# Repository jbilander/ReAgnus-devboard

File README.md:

# ReAgnus-devboard
A development board for ReAgnus<br />

Compatible with the [PLCC-84-plug](https://github.com/jbilander/PLCC-84-plug)

With this board you can signal tap a real Agnus chip by having a real Agnus IC in one socket and ReAgnus in the other.

***

REV 1C

<br />

<br />

<br />

<br />

***

[![CC BY-SA 4.0][cc-by-sa-shield]][cc-by-sa]

This work is licensed under a
[Creative Commons Attribution-ShareAlike 4.0 International License][cc-by-sa].

[![CC BY-SA 4.0][cc-by-sa-image]][cc-by-sa]

[cc-by-sa]: http://creativecommons.org/licenses/by-sa/4.0/
[cc-by-sa-image]: https://licensebuttons.net/l/by-sa/4.0/88x31.png
[cc-by-sa-shield]: https://img.shields.io/badge/License-CC%20BY--SA%204.0-lightgrey.svg

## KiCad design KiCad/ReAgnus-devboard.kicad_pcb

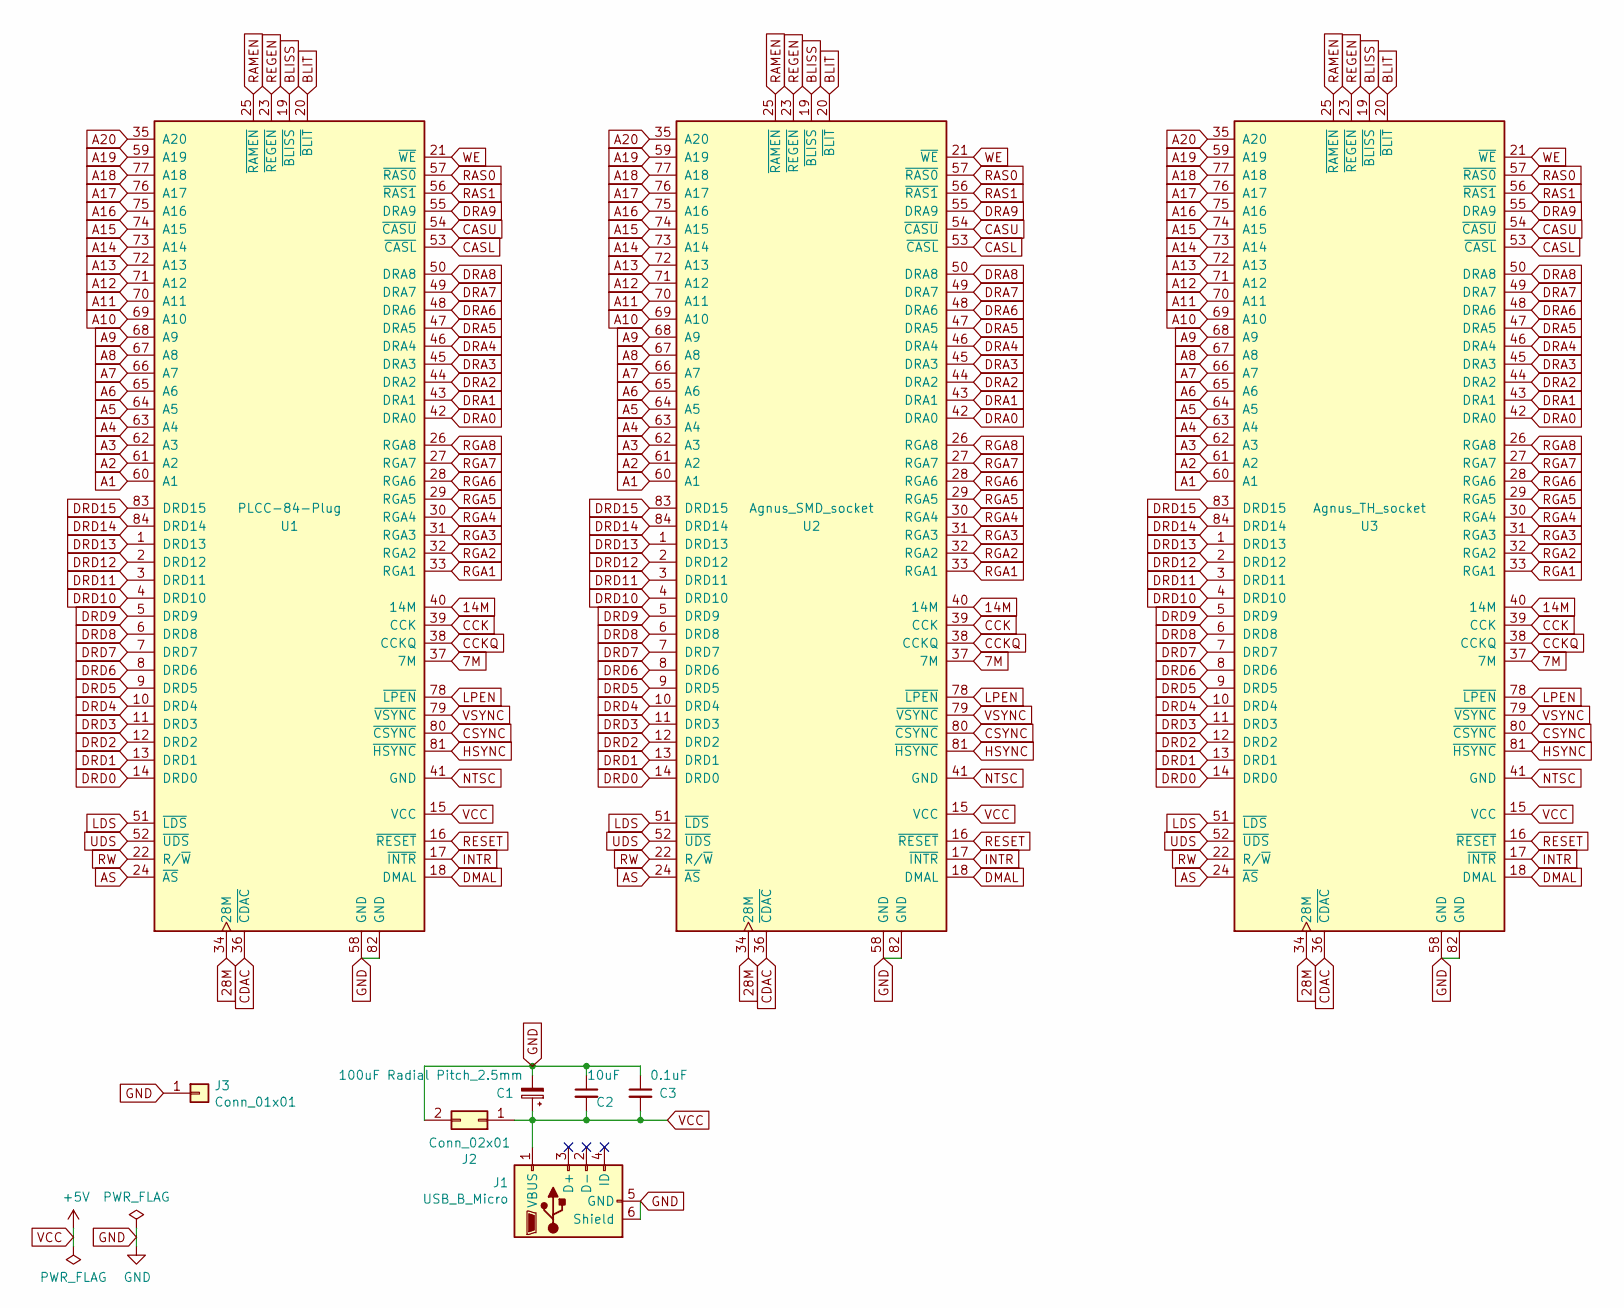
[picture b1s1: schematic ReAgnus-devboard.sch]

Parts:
C1: 100uF Radial Pitch_2.5mm; CP_Radial_D5.0mm_P2.50mm
C2: 10uF; C_1206_3216Metric_Pad1.33x1.80mm_HandSolder
C3: 0.1uF; C_0805_2012Metric_Pad1.18x1.45mm_HandSolder
J1: USB_B_Micro; USB_Micro-B_Unknown_5s_SMT
J2: Conn_02x01; PinHeader_2x01_P2.54mm_Vertical
J3: Conn_01x01; MountingHole_3.2mm_M3_Pad_Via
U1: PLCC-84-Plug; PLCC-84_Plug_P1.27mm_mirrored
U2: Agnus_SMD_socket; PLCC-84_SMD-Socket_TH_modded
U3: Agnus_TH_socket; PLCC-84_THT-Socket

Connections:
7M: U1.37 (7M), U2.37 (7M), U3.37 (7M)
14M: U1.40 (14M), U2.40 (14M), U3.40 (14M)
28M: U1.34 (28M), U2.34 (28M), U3.34 (28M)
A1: U1.60 (A1), U2.60 (A1), U3.60 (A1)
A2: U1.61 (A2), U2.61 (A2), U3.61 (A2)
A3: U1.62 (A3), U2.62 (A3), U3.62 (A3)
A4: U1.63 (A4), U2.63 (A4), U3.63 (A4)
A5: U1.64 (A5), U2.64 (A5), U3.64 (A5)
A6: U1.65 (A6), U2.65 (A6), U3.65 (A6)
A7: U1.66 (A7), U2.66 (A7), U3.66 (A7)
A8: U1.67 (A8), U2.67 (A8), U3.67 (A8)
A9: U1.68 (A9), U2.68 (A9), U3.68 (A9)
A10: U1.69 (A10), U2.69 (A10), U3.69 (A10)
A11: U1.70 (A11), U2.70 (A11), U3.70 (A11)
A12: U1.71 (A12), U2.71 (A12), U3.71 (A12)
A13: U1.72 (A13), U2.72 (A13), U3.72 (A13)
A14: U1.73 (A14), U2.73 (A14), U3.73 (A14)
A15: U1.74 (A15), U2.74 (A15), U3.74 (A15)
A16: U1.75 (A16), U2.75 (A16), U3.75 (A16)
A17: U1.76 (A17), U2.76 (A17), U3.76 (A17)
A18: U1.77 (A18), U2.77 (A18), U3.77 (A18)
A19: U1.59 (A19), U2.59 (A19), U3.59 (A19)
A20: U1.35 (A20), U2.35 (A20), U3.35 (A20)
AS: U1.24 (~AS), U2.24 (~AS), U3.24 (~AS)
BLISS: U1.19 (~BLISS), U2.19 (~BLISS), U3.19 (~BLISS)
BLIT: U1.20 (~BLIT), U2.20 (~BLIT), U3.20 (~BLIT)
CASL: U1.53 (~CASL), U2.53 (~CASL), U3.53 (~CASL)
CASU: U1.54 (~CASU), U2.54 (~CASU), U3.54 (~CASU)
CCK: U1.39 (CCK), U2.39 (CCK), U3.39 (CCK)
CCKQ: U1.38 (CCKQ), U2.38 (CCKQ), U3.38 (CCKQ)
CDAC: U1.36 (~CDAC), U2.36 (~CDAC), U3.36 (~CDAC)
CSYNC: U1.80 (~CSYNC), U2.80 (~CSYNC), U3.80 (~CSYNC)
DMAL: U1.18 (DMAL), U2.18 (DMAL), U3.18 (DMAL)
DRA0: U1.42 (DRA0), U2.42 (DRA0), U3.42 (DRA0)
DRA1: U1.43 (DRA1), U2.43 (DRA1), U3.43 (DRA1)
DRA2: U1.44 (DRA2), U2.44 (DRA2), U3.44 (DRA2)
DRA3: U1.45 (DRA3), U2.45 (DRA3), U3.45 (DRA3)
DRA4: U1.46 (DRA4), U2.46 (DRA4), U3.46 (DRA4)
DRA5: U1.47 (DRA5), U2.47 (DRA5), U3.47 (DRA5)
DRA6: U1.48 (DRA6), U2.48 (DRA6), U3.48 (DRA6)
DRA7: U1.49 (DRA7), U2.49 (DRA7), U3.49 (DRA7)
DRA8: U1.50 (DRA8), U2.50 (DRA8), U3.50 (DRA8)
DRA9: U1.55 (DRA9), U2.55 (DRA9), U3.55 (DRA9)
DRD0: U1.14 (DRD0), U2.14 (DRD0), U3.14 (DRD0)
DRD1: U1.13 (DRD1), U2.13 (DRD1), U3.13 (DRD1)
DRD2: U1.12 (DRD2), U2.12 (DRD2), U3.12 (DRD2)
DRD3: U1.11 (DRD3), U2.11 (DRD3), U3.11 (DRD3)
DRD4: U1.10 (DRD4), U2.10 (DRD4), U3.10 (DRD4)
DRD5: U1.9 (DRD5), U2.9 (DRD5), U3.9 (DRD5)
DRD6: U1.8 (DRD6), U2.8 (DRD6), U3.8 (DRD6)
DRD7: U1.7 (DRD7), U2.7 (DRD7), U3.7 (DRD7)
DRD8: U1.6 (DRD8), U2.6 (DRD8), U3.6 (DRD8)
DRD9: U1.5 (DRD9), U2.5 (DRD9), U3.5 (DRD9)
DRD10: U1.4 (DRD10), U2.4 (DRD10), U3.4 (DRD10)
DRD11: U1.3 (DRD11), U2.3 (DRD11), U3.3 (DRD11)
DRD12: U1.2 (DRD12), U2.2 (DRD12), U3.2 (DRD12)
DRD13: U1.1 (DRD13), U2.1 (DRD13), U3.1 (DRD13)
DRD14: U1.84 (DRD14), U2.84 (DRD14), U3.84 (DRD14)
DRD15: U1.83 (DRD15), U2.83 (DRD15), U3.83 (DRD15)
GND: C1.2, C2.1, C3.1, J1.5 (GND), J1.6 (Shield), J2.2, J3.1, U1.58 (GND), U1.82 (GND), U2.58 (GND), U2.82 (GND), U3.58 (GND), U3.82 (GND)
HSYNC: U1.81 (~HSYNC), U2.81 (~HSYNC), U3.81 (~HSYNC)
INTR: U1.17 (~INTR), U2.17 (~INTR), U3.17 (~INTR)
LDS: U1.51 (~LDS), U2.51 (~LDS), U3.51 (~LDS)
LPEN: U1.78 (~LPEN), U2.78 (~LPEN), U3.78 (~LPEN)
NTSC: U1.41 (GND), U2.41 (GND), U3.41 (GND)
RAMEN: U1.25 (~RAMEN), U2.25 (~RAMEN), U3.25 (~RAMEN)
RAS0: U1.57 (~RAS0), U2.57 (~RAS0), U3.57 (~RAS0)
RAS1: U1.56 (~RAS1), U2.56 (~RAS1), U3.56 (~RAS1)
REGEN: U1.23 (~REGEN), U2.23 (~REGEN), U3.23 (~REGEN)
RESET: U1.16 (~RESET), U2.16 (~RESET), U3.16 (~RESET)
RGA1: U1.33 (RGA1), U2.33 (RGA1), U3.33 (RGA1)
RGA2: U1.32 (RGA2), U2.32 (RGA2), U3.32 (RGA2)
RGA3: U1.31 (RGA3), U2.31 (RGA3), U3.31 (RGA3)
RGA4: U1.30 (RGA4), U2.30 (RGA4), U3.30 (RGA4)
RGA5: U1.29 (RGA5), U2.29 (RGA5), U3.29 (RGA5)
RGA6: U1.28 (RGA6), U2.28 (RGA6), U3.28 (RGA6)
RGA7: U1.27 (RGA7), U2.27 (RGA7), U3.27 (RGA7)
RGA8: U1.26 (RGA8), U2.26 (RGA8), U3.26 (RGA8)
RW: U1.22 (R/~W), U2.22 (R/~W), U3.22 (R/~W)
UDS: U1.52 (~UDS), U2.52 (~UDS), U3.52 (~UDS)
VCC: C1.1, C2.2, C3.2, J1.1 (VBUS), J2.1, U1.15 (VCC), U2.15 (VCC), U3.15 (VCC)
VSYNC: U1.79 (~VSYNC), U2.79 (~VSYNC), U3.79 (~VSYNC)
WE: U1.21 (~WE), U2.21 (~WE), U3.21 (~WE)

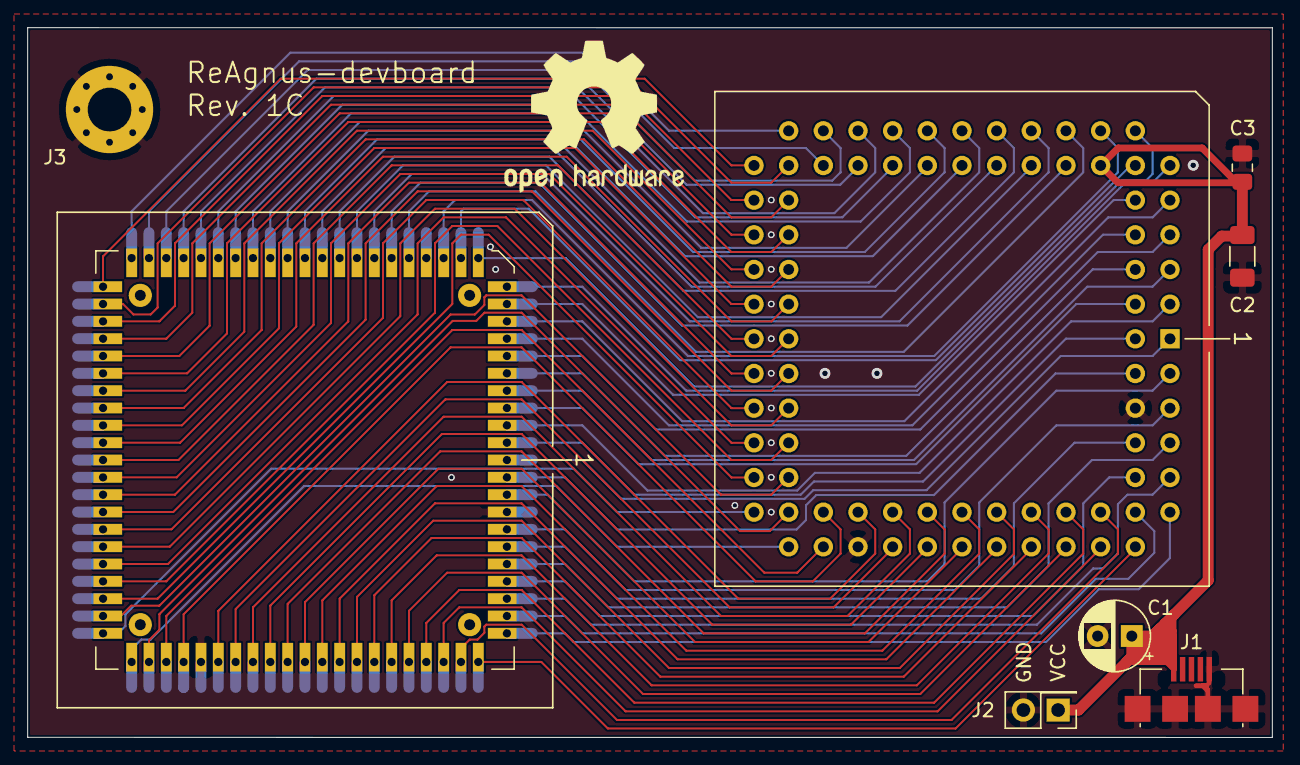
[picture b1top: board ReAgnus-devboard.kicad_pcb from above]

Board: 4 copper layers, 91.2 x 52.0 mm, 9 parts (1 on the bottom side), 83 nets.

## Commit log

2021-06-24 added KiCad files
2021-06-29 added power jacks, rerouted with 6 mil tracks
2021-07-18 Removed unnecessary folder
2021-07-18 added license file
2021-08-01 Resized footprint somewhat to better fit with homebrew PLCC-84-plug support PCB using TH-pins
2021-08-19 added pics
2021-09-08 Added a microUSB jack for power supply
2021-09-08 updated pics to Rev. 1B
2021-09-14 Changed to 0.6mm holes, the spacing between hole and trace was less than 0.254mm, which is out of production capability
2021-09-14 updated pics
2024-08-30 add images
2024-08-30 nuke old design
2024-08-30 Add new design
2024-08-30 Update file
